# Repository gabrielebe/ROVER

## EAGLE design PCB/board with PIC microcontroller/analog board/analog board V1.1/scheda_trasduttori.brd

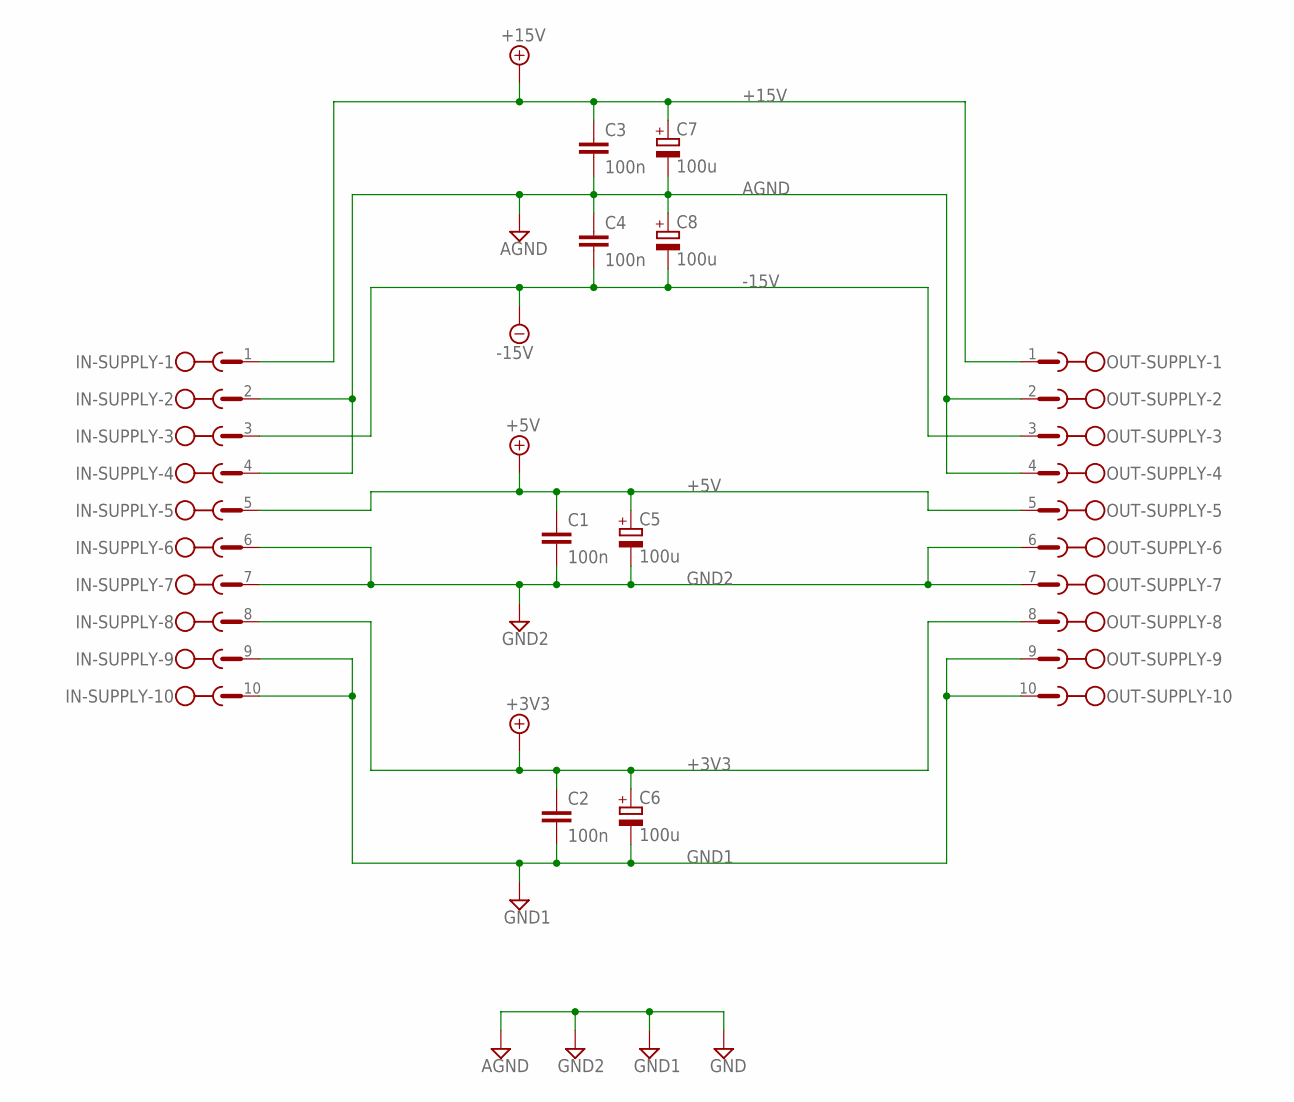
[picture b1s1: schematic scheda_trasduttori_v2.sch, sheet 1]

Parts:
C1, C2, C3, C4: 100n; C2.5-3
C5, C6, C7, C8: 100u; E2,5-7
IN-SUPPLY: MSTBA10
OUT-SUPPLY: MSTBA10

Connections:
+3V3: C2.1, C6.+, IN-SUPPLY.8, OUT-SUPPLY.8; also elsewhere on the board
+5V: C1.1, C5.+, IN-SUPPLY.5, OUT-SUPPLY.5; also elsewhere on the board
+15V: C3.1, C7.+, IN-SUPPLY.1, OUT-SUPPLY.1; also elsewhere on the board
-15V: C4.2, C8.-, IN-SUPPLY.3, OUT-SUPPLY.3; also elsewhere on the board
AGND: C3.2, C4.1, C7.-, C8.+, IN-SUPPLY.2, IN-SUPPLY.4, OUT-SUPPLY.2, OUT-SUPPLY.4; also elsewhere on the board
GND1: C2.2, C6.-, IN-SUPPLY.9, IN-SUPPLY.10, OUT-SUPPLY.9, OUT-SUPPLY.10; also elsewhere on the board
GND2: C1.2, C5.-, IN-SUPPLY.6, IN-SUPPLY.7, OUT-SUPPLY.6, OUT-SUPPLY.7; also elsewhere on the board

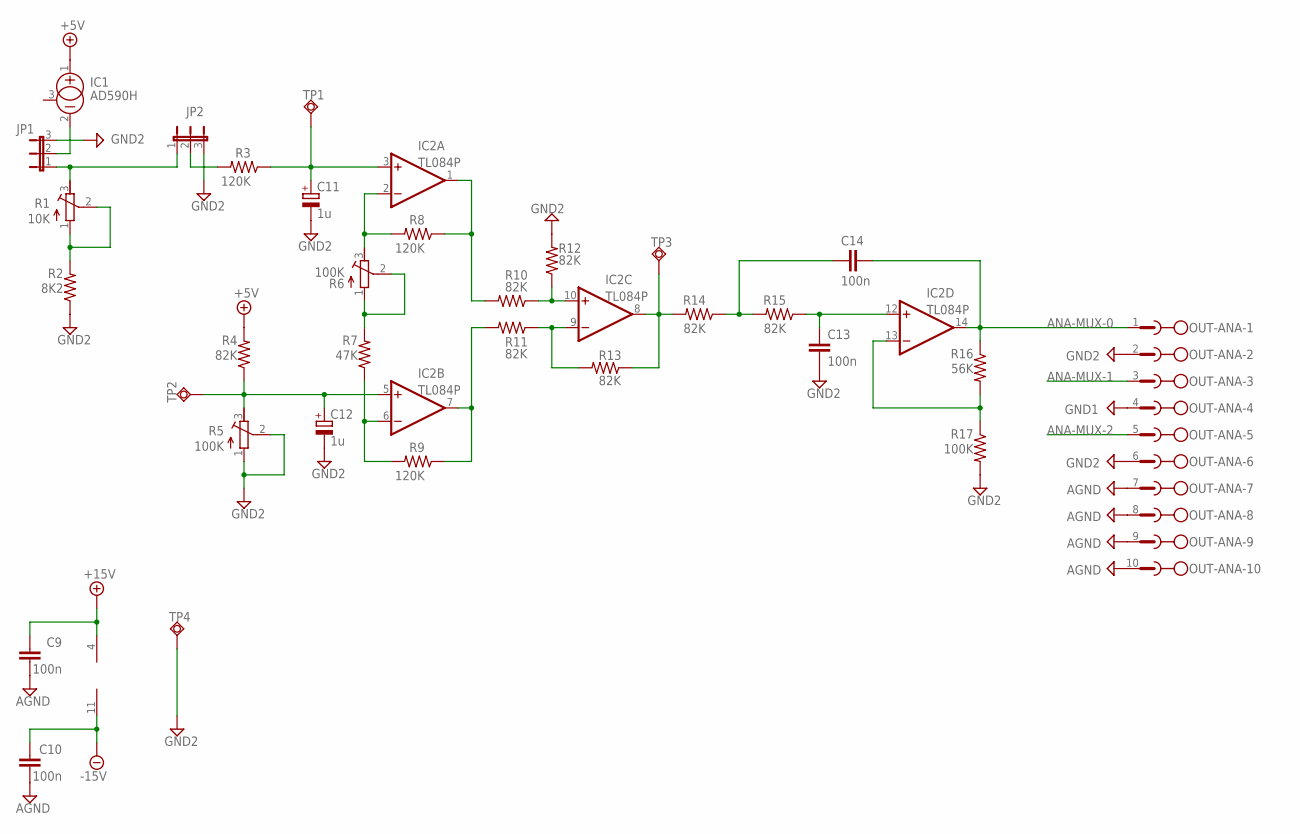
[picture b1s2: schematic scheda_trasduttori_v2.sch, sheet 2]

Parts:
C9, C10, C13, C14: 100n; C025-024X044
C11, C12: 1u; E5-8,5
IC1: AD590H; TO18
IC2: TL084P; DIL14
JP1, JP2: JP2E; JP2
OUT-ANA: MSTBA10
R1: 10K; RTRIM64W
R2: 8K2; 0204/7
R3, R8, R9: 120K; 0204/7
R4, R10, R11, R12, R13, R14, R15: 82K; 0204/7
R5, R6: 100K; RTRIM64W
R7: 47K; 0204/7
R16: 56K; 0204/7
R17: 100K; 0204/7
TP1, TP2, TP3, TP4: TPSQPAD1-17Y; P1-17Y

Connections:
+5V: IC1.1 (+), R4.2; also elsewhere on the board
+15V: C9.2, IC2.4 (V+); also elsewhere on the board
-15V: C10.2, IC2.11 (V-); also elsewhere on the board
AGND: C9.1, C10.1, OUT-ANA.7, OUT-ANA.8, OUT-ANA.9, OUT-ANA.10; also elsewhere on the board
ANA-MUX-0: C14.2, IC2.14 (OUT), OUT-ANA.1, R16.1
GND2: C11.-, C12.-, C13.1, JP1.3, JP2.3, OUT-ANA.2, OUT-ANA.6, R2.1, R5.1 (E), R5.2 (S), R12.2, R17.2, TP4.TP; also elsewhere on the board
unnamed: R1.1 (E), R1.2 (S), R2.2
unnamed: IC1.2 (-), JP1.2
unnamed: R6.1 (E), R6.2 (S), R7.2
unnamed 14: C11.+, IC2.3 (+IN), R3.1, TP1.TP; also elsewhere on the board
unnamed: IC2.2 (-IN), R6.3 (A), R8.2
unnamed: IC2.1 (OUT), R8.1, R10.2
unnamed: JP2.2, R3.2
unnamed: JP1.1, JP2.1, R1.3 (A)
unnamed 19: C12.+, IC2.5 (+IN), R4.1, R5.3 (A), TP2.TP; also elsewhere on the board
unnamed: IC2.6 (-IN), R7.1, R9.2
unnamed: IC2.7 (OUT), R9.1, R11.2
unnamed: IC2.10 (+IN), R10.1, R12.1
unnamed: IC2.9 (-IN), R11.1, R13.2
unnamed 24: IC2.8 (OUT), R13.1, R14.2, TP3.TP; also elsewhere on the board
unnamed: C14.1, R14.1, R15.2
unnamed: C13.2, IC2.12 (+IN), R15.1
unnamed: IC2.13 (-IN), R16.2, R17.1

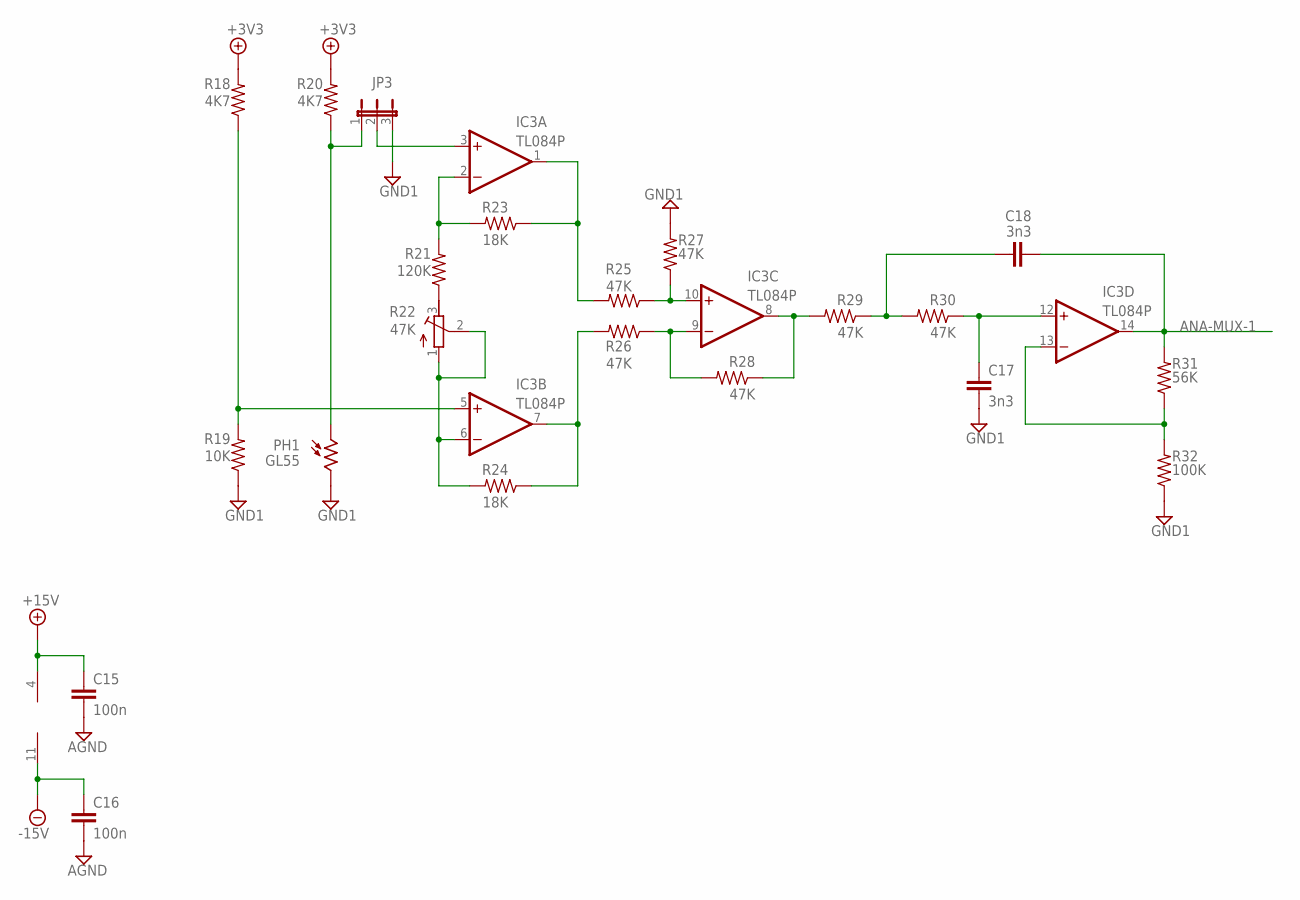
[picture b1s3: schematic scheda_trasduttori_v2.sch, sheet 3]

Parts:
C15, C16: 100n; C025-025X050
C17, C18: 3n3; C025-025X050
IC3: TL084P; DIL14
JP3: JP2E; JP2
PH1: GL55; T0-46-A10XX
R18, R20: 4K7; 0204/7
R19: 10K; 0204/7
R21: 120K; 0204/7
R22: 47K; RTRIM64W
R23, R24: 18K; 0204/7
R25, R26, R27, R28, R29, R30: 47K; 0204/7
R31: 56K; 0204/7
R32: 100K; 0204/7

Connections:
+4.1V: R18.2, R20.2
+15V: C15.1, IC3.4 (V+); also elsewhere on the board
-15V: C16.1, IC3.11 (V-); also elsewhere on the board
AGND: C15.2, C16.2; also elsewhere on the board
ANA-MUX-1: C18.2, IC3.14 (OUT), R31.2
GND1: C17.2, JP3.3, PH1.2, R19.1, R27.2, R32.1; also elsewhere on the board
unnamed: IC3.5 (+IN), R18.1, R19.2
unnamed: JP3.1, PH1.1, R20.1
unnamed: R21.1, R22.3 (A)
unnamed: IC3.6 (-IN), R22.1 (E), R22.2 (S), R24.2
unnamed: IC3.7 (OUT), R24.1, R26.2
unnamed: IC3.1 (OUT), R23.1, R25.2
unnamed: IC3.2 (-IN), R21.2, R23.2
unnamed: IC3.10 (+IN), R25.1, R27.1
unnamed: IC3.9 (-IN), R26.1, R28.2
unnamed: IC3.8 (OUT), R28.1, R29.2
unnamed: C17.1, IC3.12 (+IN), R30.1
unnamed: IC3.13 (-IN), R31.1, R32.2
unnamed: C18.1, R29.1, R30.2
unnamed: IC3.3 (+IN), JP3.2

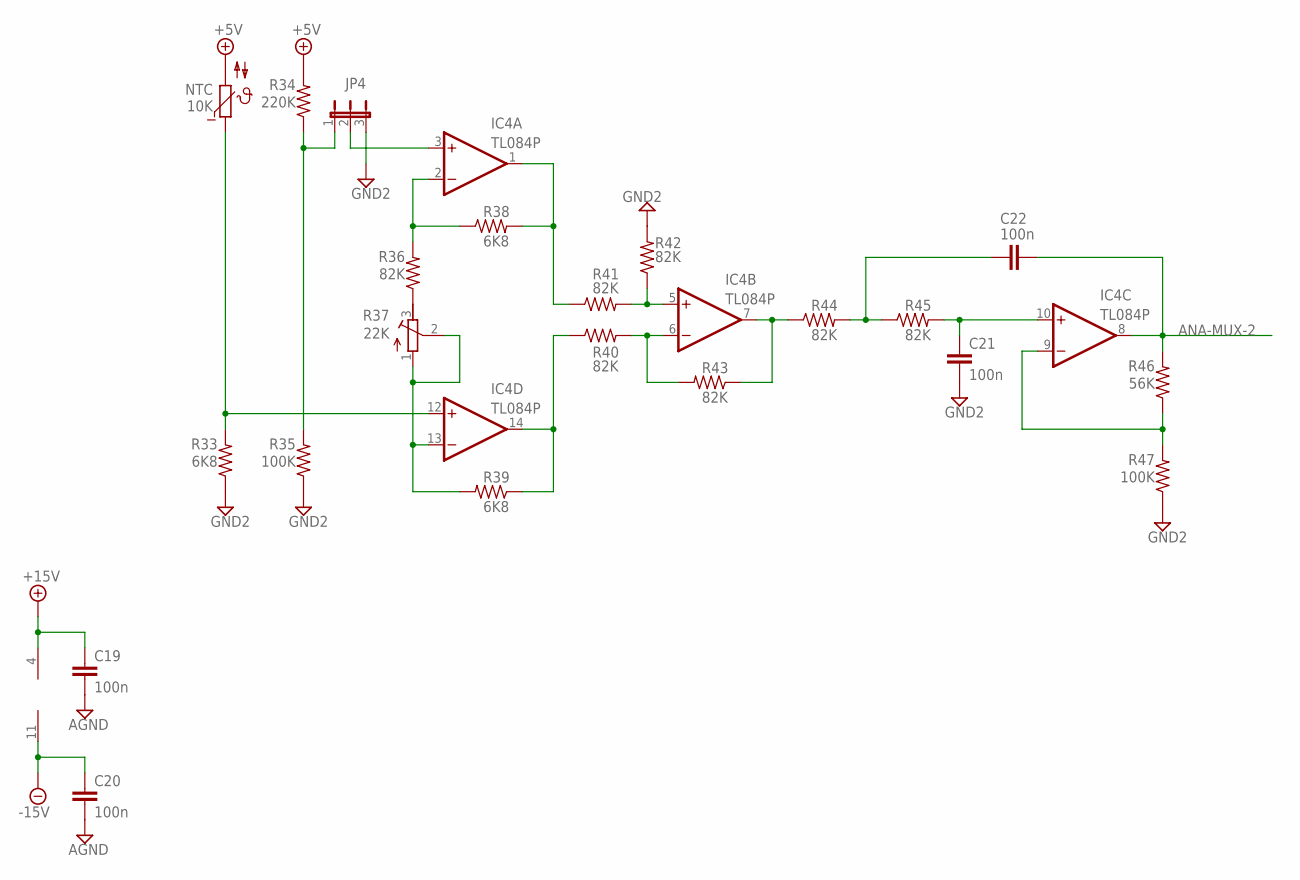
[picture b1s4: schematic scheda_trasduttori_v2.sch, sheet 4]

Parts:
C19, C20, C21, C22: 100n; C025-025X050
IC4: TL084P; DIL14
JP4: JP2E; JP2
NTC: 10K; P640
R33, R38, R39: 6K8; 0204/7
R34: 220K; 0204/7
R35, R47: 100K; 0204/7
R36, R40, R41, R42, R43, R44, R45: 82K; 0204/7
R37: 22K; RTRIM64W
R46: 56K; 0204/7

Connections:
+5V: NTC.2, R34.2; also elsewhere on the board
+15V: C19.1, IC4.4 (V+); also elsewhere on the board
-15V: C20.1, IC4.11 (V-); also elsewhere on the board
AGND: C19.2, C20.2; also elsewhere on the board
ANA-MUX-2: C22.2, IC4.8 (OUT), R46.2
GND2: C21.2, JP4.3, R33.1, R35.1, R42.2, R47.1; also elsewhere on the board
unnamed: C21.1, IC4.10 (+IN), R45.2
unnamed: IC4.9 (-IN), R46.1, R47.2
unnamed: C22.1, R44.2, R45.1
unnamed: IC4.12 (+IN), NTC.1, R33.2
unnamed: R36.1, R37.3 (A)
unnamed: IC4.2 (-IN), R36.2, R38.1
unnamed: IC4.1 (OUT), R38.2, R40.1
unnamed: IC4.13 (-IN), R37.1 (E), R37.2 (S), R39.2
unnamed: IC4.14 (OUT), R39.1, R41.1
unnamed: IC4.6 (-IN), R41.2, R43.2
unnamed: IC4.5 (+IN), R40.2, R42.1
unnamed: IC4.7 (OUT), R43.1, R44.1
unnamed: JP4.1, R34.1, R35.2
unnamed: IC4.3 (+IN), JP4.2

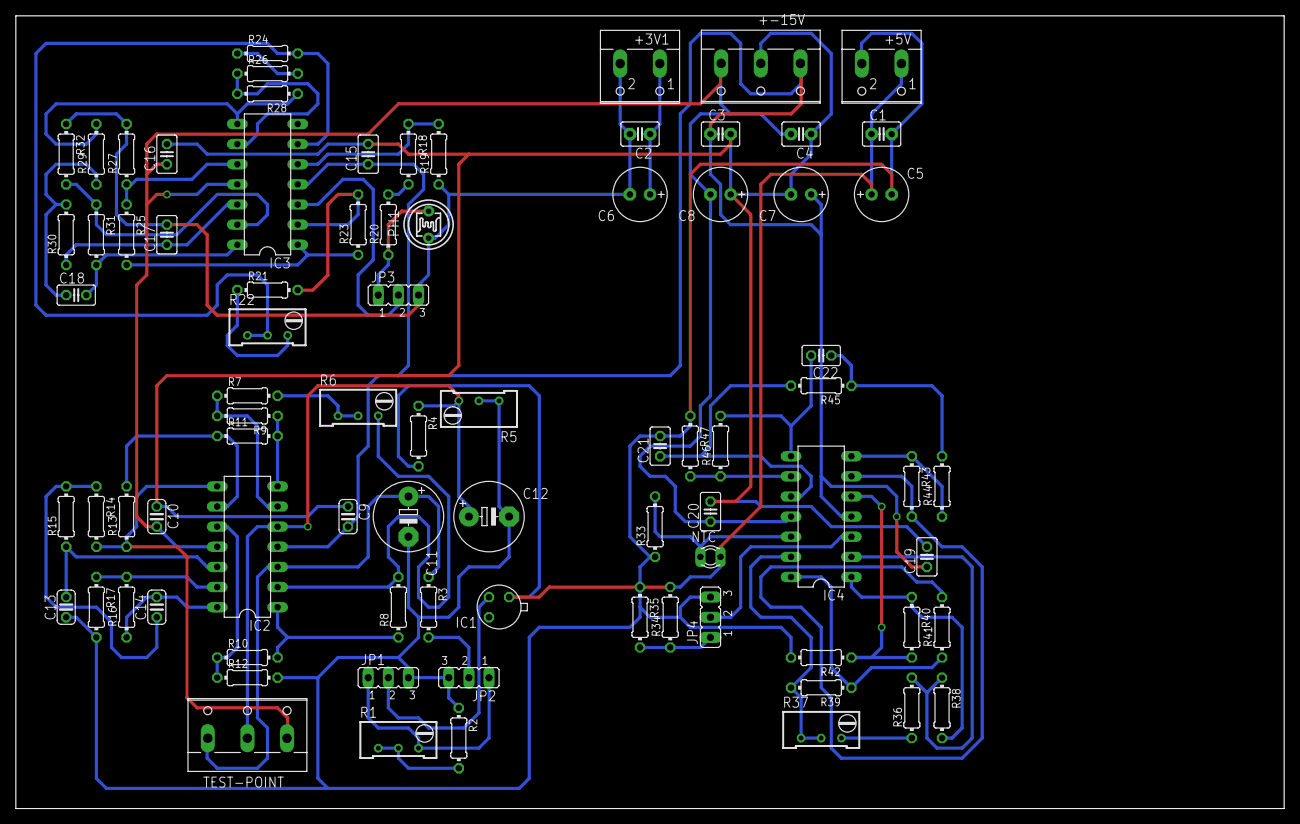
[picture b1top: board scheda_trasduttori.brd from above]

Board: 2 copper layers, 160.0 x 100.0 mm, 83 parts (0 on the bottom side), 56 nets.

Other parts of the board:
+3V1, +5V: W237-102
+-15V: W237-103
TEST-POINT: W237-103

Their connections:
+3V3: +3V1.1; also elsewhere on the board
+5V: +5V.1; also elsewhere on the board
+15V: +-15V.1; also elsewhere on the board
-15V: +-15V.3; also elsewhere on the board
AGND: +-15V.2; also elsewhere on the board
GND1: +3V1.2; also elsewhere on the board
GND2: +5V.2; also elsewhere on the board
unnamed 14: TEST-POINT.1; also elsewhere on the board
unnamed 19: TEST-POINT.2; also elsewhere on the board
unnamed 24: TEST-POINT.3; also elsewhere on the board

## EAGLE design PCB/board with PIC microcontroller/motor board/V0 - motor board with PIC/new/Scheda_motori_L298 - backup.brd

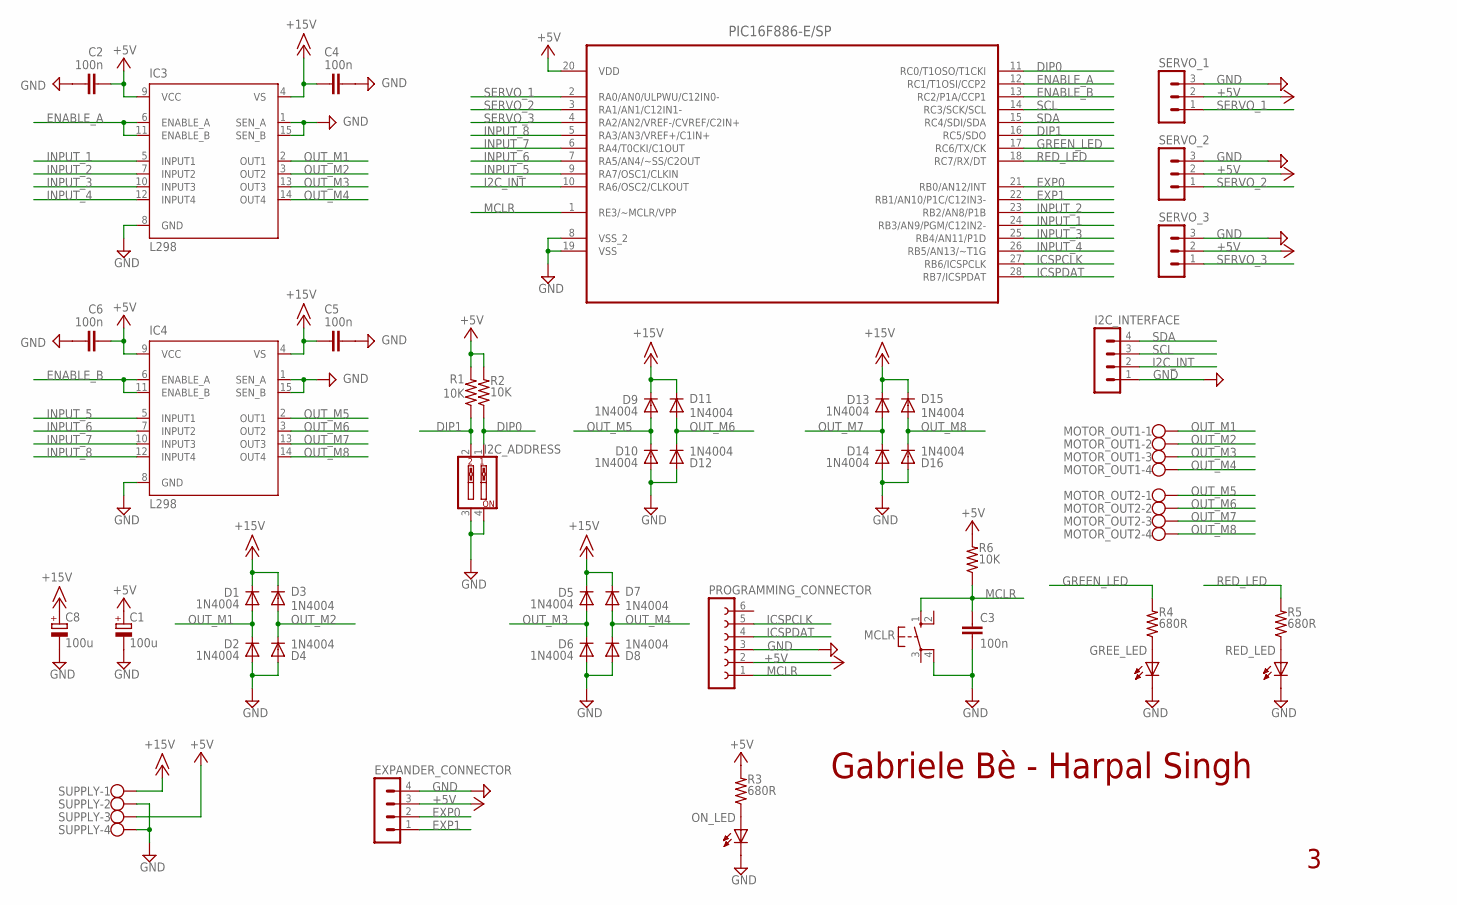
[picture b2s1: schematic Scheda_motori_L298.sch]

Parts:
C1, C8: 100u; E2,5-7
C2, C3, C4, C5, C6: 100n; C050-024X044
D1, D2, D3, D4, D5, D6, D7, D8, D9, D10, D11, D12, D13, D14, D15, D16: 1N4004; DO41-10
EXPANDER_CONNECTOR: MA04-1
GREE_LED: HLMP6
I2C_ADDRESS: SW_DIP-2; EDG-02
I2C_INTERFACE: MA04-1
IC3, IC4: L298; MULTIWATT-15
MCLR: 10-XX; B3F-10XX
MOTOR_OUT1, MOTOR_OUT2: W237-4
ON_LED: HLMP6
PROGRAMMING_CONNECTOR: FE06-1; FE06
R1, R2, R6: 10K; 0207/10
R3, R4, R5: 680R; 0207/10
RED_LED: HLMP6
SERVO_1, SERVO_2, SERVO_3: MA03-1
SUPPLY: W237-4
U$1: PIC16F886-E/SP; DIP254P762X508-28

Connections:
+5V: C1.+, C2.2, C6.2, EXPANDER_CONNECTOR.3, IC3.9 (VCC), IC4.9 (VCC), PROGRAMMING_CONNECTOR.2, R1.2, R2.2, R3.2, R6.2, SERVO_1.2, SERVO_2.2, SERVO_3.2, SUPPLY.3, U$1.20 (VDD)
+15V: C4.1, C5.1, C8.+, D1.C, D3.C, D5.C, D7.C, D9.C, D11.C, D13.C, D15.C, IC3.4 (VS), IC4.4 (VS), SUPPLY.1
DIP0: I2C_ADDRESS.1, R2.1, U$1.11 (RC0/T1OSO/T1CKI)
DIP1: I2C_ADDRESS.2, R1.1, U$1.16 (RC5/SDO)
ENABLE_A: IC3.6 (ENABLE_A), IC3.11 (ENABLE_B), U$1.12 (RC1/T1OSI/CCP2)
ENABLE_B: IC4.6 (ENABLE_A), IC4.11 (ENABLE_B), U$1.13 (RC2/P1A/CCP1)
EXP0: EXPANDER_CONNECTOR.2, U$1.21 (RB0/AN12/INT)
EXP1: EXPANDER_CONNECTOR.1, U$1.22 (RB1/AN10/P1C/C12IN3-)
GND: C1.-, C2.1, C3.2, C4.2, C5.2, C6.1, C8.-, D2.A, D4.A, D6.A, D8.A, D10.A, D12.A, D14.A, D16.A, EXPANDER_CONNECTOR.4, GREE_LED.K, I2C_ADDRESS.3, I2C_ADDRESS.4, I2C_INTERFACE.1, IC3.1 (SEN_A), IC3.8 (GND), IC3.15 (SEN_B), IC4.1 (SEN_A), IC4.8 (GND), IC4.15 (SEN_B), MCLR.4 (P1), ON_LED.K, PROGRAMMING_CONNECTOR.3, RED_LED.K, SERVO_1.3, SERVO_2.3, SERVO_3.3, SUPPLY.2, SUPPLY.4, U$1.8 (VSS_2), U$1.19 (VSS)
GREEN_LED: R4.2, U$1.17 (RC6/TX/CK)
I2C_INT: I2C_INTERFACE.2, U$1.10 (RA6/OSC2/CLKOUT)
ICSPCLK: PROGRAMMING_CONNECTOR.5, U$1.27 (RB6/ICSPCLK)
ICSPDAT: PROGRAMMING_CONNECTOR.4, U$1.28 (RB7/ICSPDAT)
INPUT_1: IC3.5 (INPUT1), U$1.24 (RB3/AN9/PGM/C12IN2-)
INPUT_2: IC3.7 (INPUT2), U$1.23 (RB2/AN8/P1B)
INPUT_3: IC3.10 (INPUT3), U$1.25 (RB4/AN11/P1D)
INPUT_4: IC3.12 (INPUT4), U$1.26 (RB5/AN13/~T1G)
INPUT_5: IC4.5 (INPUT1), U$1.9 (RA7/OSC1/CLKIN)
INPUT_6: IC4.7 (INPUT2), U$1.7 (RA5/AN4/~SS/C2OUT)
INPUT_7: IC4.10 (INPUT3), U$1.6 (RA4/T0CKI/C1OUT)
INPUT_8: IC4.12 (INPUT4), U$1.5 (RA3/AN3/VREF+/C1IN+)
MCLR: C3.1, MCLR.1 (S), PROGRAMMING_CONNECTOR.1, R6.1, U$1.1 (RE3/~MCLR/VPP)
unnamed: ON_LED.A, R3.1
unnamed: GREE_LED.A, R4.1
unnamed: R5.1, RED_LED.A
OUT_M1: D1.A, D2.C, IC3.2 (OUT1), MOTOR_OUT1.1
OUT_M2: D3.A, D4.C, IC3.3 (OUT2), MOTOR_OUT1.2
OUT_M3: D5.A, D6.C, IC3.13 (OUT3), MOTOR_OUT1.3
OUT_M4: D7.A, D8.C, IC3.14 (OUT4), MOTOR_OUT1.4
OUT_M5: D9.A, D10.C, IC4.2 (OUT1), MOTOR_OUT2.1
OUT_M6: D11.A, D12.C, IC4.3 (OUT2), MOTOR_OUT2.2
OUT_M7: D13.A, D14.C, IC4.13 (OUT3), MOTOR_OUT2.3
OUT_M8: D15.A, D16.C, IC4.14 (OUT4), MOTOR_OUT2.4
RED_LED: R5.2, U$1.18 (RC7/RX/DT)
SCL: I2C_INTERFACE.3, U$1.14 (RC3/SCK/SCL)
SDA: I2C_INTERFACE.4, U$1.15 (RC4/SDI/SDA)
SERVO_1: SERVO_1.1, U$1.2 (RA0/AN0/ULPWU/C12IN0-)
SERVO_2: SERVO_2.1, U$1.3 (RA1/AN1/C12IN1-)
SERVO_3: SERVO_3.1, U$1.4 (RA2/AN2/VREF-/CVREF/C2IN+)

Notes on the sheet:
Gabriele Bè - Harpal Singh

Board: 2 copper layers, 46 parts (0 on the bottom side), 39 nets, no tracks yet.

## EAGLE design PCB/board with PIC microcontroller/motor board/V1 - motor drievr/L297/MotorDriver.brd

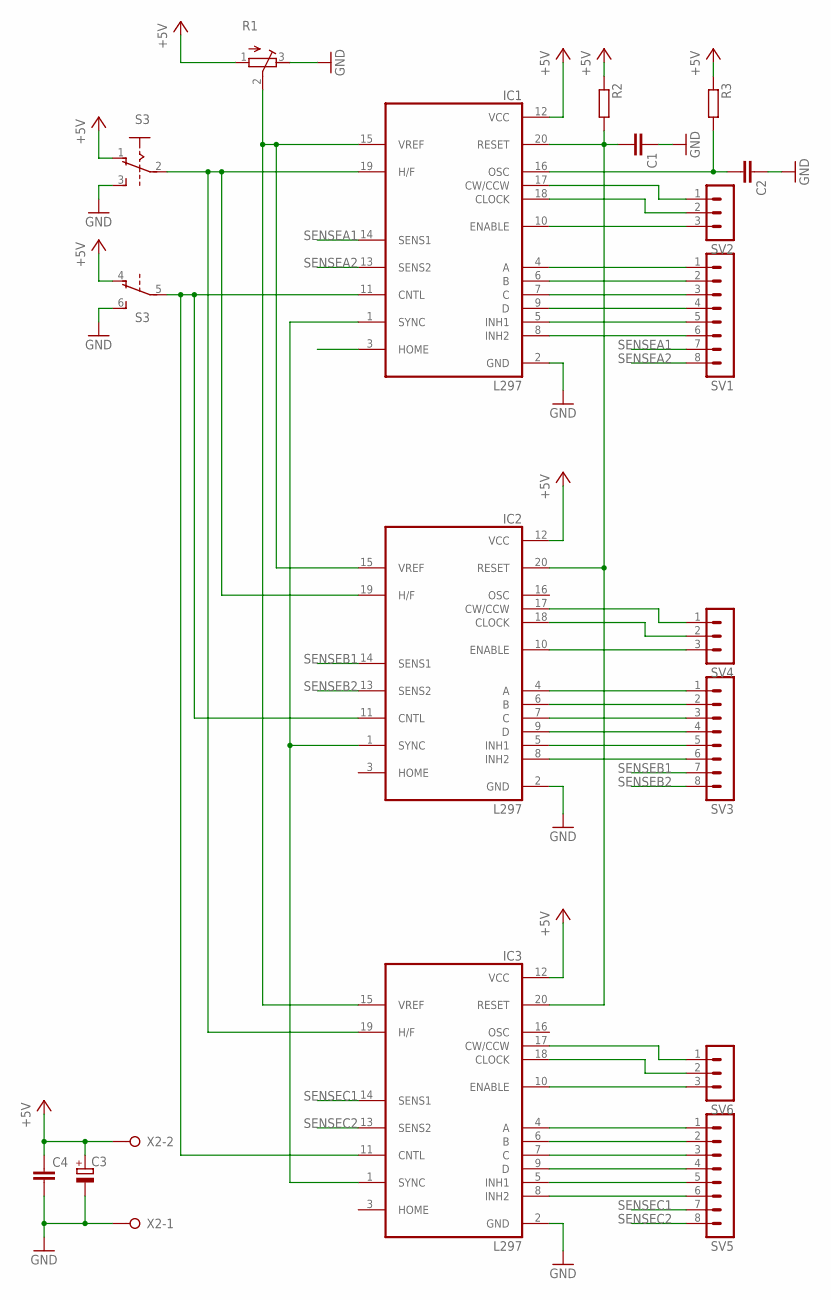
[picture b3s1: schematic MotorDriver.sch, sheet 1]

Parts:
C1, C2, C4: C-EU050-024X044; C050-024X044
C3: CPOL-EUE3.5-8; E3,5-8
IC1, IC2, IC3: L297; DIL20
R1: R-TRIMM64P; RTRIM64P
R2, R3: R-EU_0207/10; 0207/10
S3: A68-A31
SV1, SV3, SV5: MA08-1
SV2, SV4, SV6: MA03-1
X2: W237-02P; W237-132

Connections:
+5V: C3.+, C4.1, IC1.12 (VCC), IC2.12 (VCC), IC3.12 (VCC), R1.1 (A), R2.1, R3.1, S3.1 (O), S3.4 (O), X2.2
GND: C1.1, C2.1, C3.-, C4.2, IC1.2 (GND), IC2.2 (GND), IC3.2 (GND), R1.3 (E), S3.3 (S), S3.6 (S), X2.1
unnamed: C2.2, IC1.16 (OSC), R3.2
unnamed: IC1.4 (A), SV1.1
unnamed: IC1.6 (B), SV1.2
unnamed: IC1.7 (C), SV1.3
unnamed: IC1.9 (D), SV1.4
unnamed: IC1.5 (INH1), SV1.5
unnamed: IC1.8 (INH2), SV1.6
unnamed: IC1.17 (CW/CCW), SV2.1
unnamed: IC1.18 (CLOCK), SV2.2
unnamed: IC1.10 (ENABLE), SV2.3
unnamed: IC1.19 (H/F), IC2.19 (H/F), IC3.19 (H/F), S3.2
unnamed: IC1.11 (CNTL), IC2.11 (CNTL), IC3.11 (CNTL), S3.5
unnamed: IC1.15 (VREF), IC2.15 (VREF), IC3.15 (VREF), R1.2 (S)
unnamed: IC2.4 (A), SV3.1
unnamed: IC2.6 (B), SV3.2
unnamed: IC2.7 (C), SV3.3
unnamed: IC2.9 (D), SV3.4
unnamed: IC2.5 (INH1), SV3.5
unnamed: IC2.8 (INH2), SV3.6
unnamed: IC2.17 (CW/CCW), SV4.1
unnamed: IC2.18 (CLOCK), SV4.2
unnamed: IC2.10 (ENABLE), SV4.3
unnamed: IC1.1 (SYNC), IC2.1 (SYNC), IC3.1 (SYNC)
unnamed: C1.2, IC1.20 (RESET), IC2.20 (RESET), IC3.20 (RESET), R2.2
unnamed: IC3.4 (A), SV5.1
unnamed: IC3.6 (B), SV5.2
unnamed: IC3.7 (C), SV5.3
unnamed: IC3.9 (D), SV5.4
unnamed: IC3.5 (INH1), SV5.5
unnamed: IC3.8 (INH2), SV5.6
unnamed: IC3.17 (CW/CCW), SV6.1
unnamed: IC3.18 (CLOCK), SV6.2
unnamed: IC3.10 (ENABLE), SV6.3
SENSEA1: IC1.14 (SENS1), SV1.7
SENSEA2: IC1.13 (SENS2), SV1.8
SENSEB1: IC2.14 (SENS1), SV3.7
SENSEB2: IC2.13 (SENS2), SV3.8
SENSEC1: IC3.14 (SENS1), SV5.7
SENSEC2: IC3.13 (SENS2), SV5.8

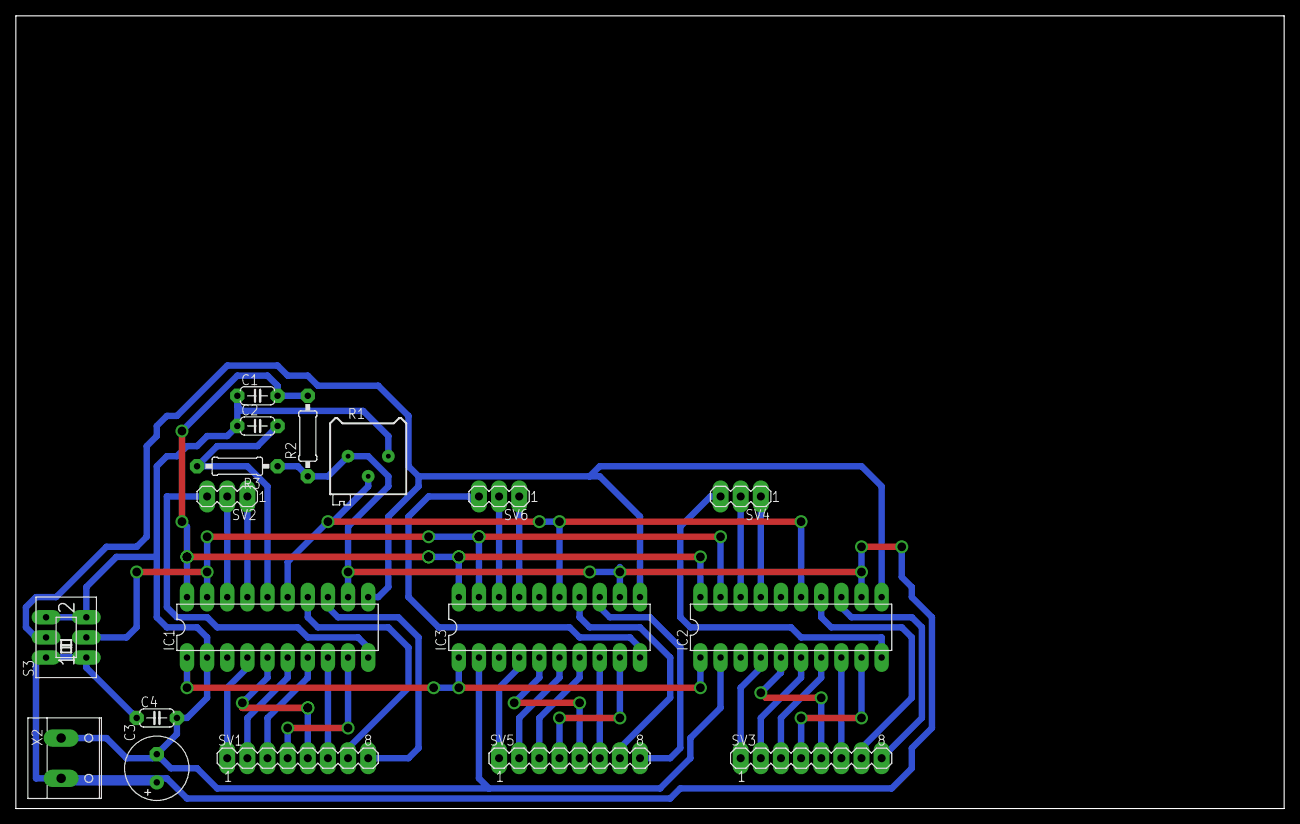
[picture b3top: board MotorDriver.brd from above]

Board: 2 copper layers, 160.0 x 100.0 mm, 18 parts (0 on the bottom side), 41 nets.

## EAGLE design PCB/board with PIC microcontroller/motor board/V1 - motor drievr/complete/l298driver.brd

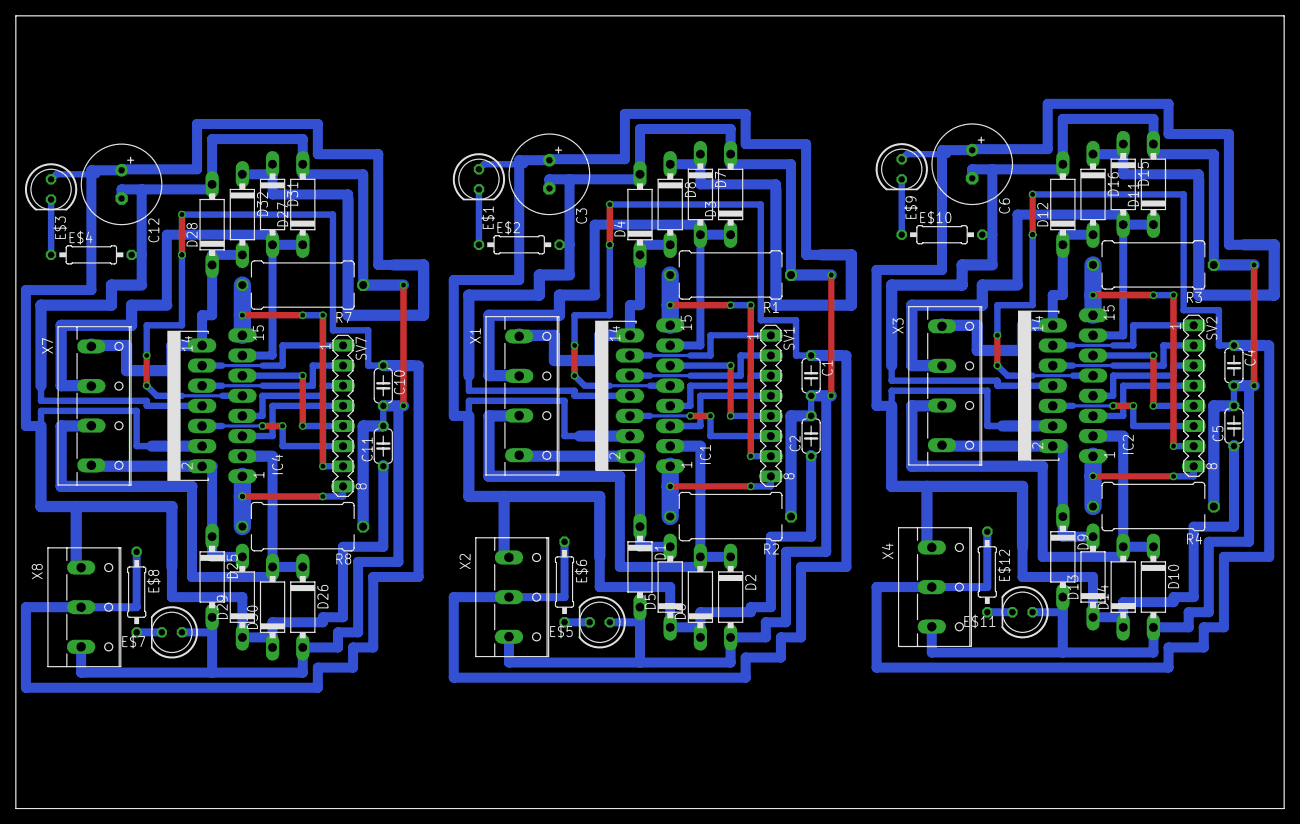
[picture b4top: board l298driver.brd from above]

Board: 2 copper layers, 160.0 x 100.0 mm, 63 parts (0 on the bottom side), 51 nets.

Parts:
C1, C2, C4, C5, C10, C11: C050-024X044
C3, C6, C12: E3,5-10
D1, D2, D3, D4, D5, D6, D7, D8, D9, D10, D11, D12, D13, D14, D15, D16, D25, D26, D27, D28, D29, D30, D31, D32: BA157; P1-10
E$1, E$3, E$5, E$7, E$9, E$11: LED5MM
E$2, E$4, E$6, E$8, E$10, E$12: 0207/10
IC1, IC2, IC4: L298; MULTIWATT-15
R1, R2, R3, R4, R7, R8: RDH/15
SV1, SV2, SV7: MA08-1
X1, X3, X7: W237-4
X2, X4, X8: W237-103

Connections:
GND1: C1.2, C2.2, C3.-, D1.A, D2.A, D3.A, D4.A, E$2.2, E$5.A, IC1.8, R1.1, R2.1, X2.3
GND2: C4.2, C5.2, C6.-, D9.A, D10.A, D11.A, D12.A, E$10.2, E$11.A, IC2.8, R3.1, R4.1, X4.3
GND3: C10.2, C11.2, C12.-, D25.A, D26.A, D27.A, D28.A, E$4.2, E$7.A, IC4.8, R7.1, R8.1, X8.3
unnamed: D1.C, D5.A, IC1.2, X1.4
unnamed: D2.C, D6.A, IC1.3, X1.3
unnamed: D3.C, D7.A, IC1.13, X1.2
unnamed: D4.C, D8.A, IC1.14, X1.1
unnamed: IC1.12, SV1.1
unnamed: IC1.10, SV1.2
unnamed: IC1.7, SV1.3
unnamed: IC1.5, SV1.4
unnamed: IC1.11, SV1.5
unnamed: IC1.6, SV1.6
unnamed: D9.C, D13.A, IC2.2, X3.4
unnamed: D10.C, D14.A, IC2.3, X3.3
unnamed: D11.C, D15.A, IC2.13, X3.2
unnamed: D12.C, D16.A, IC2.14, X3.1
unnamed: IC2.12, SV2.1
unnamed: IC2.10, SV2.2
unnamed: IC2.7, SV2.3
unnamed: IC2.5, SV2.4
unnamed: IC2.11, SV2.5
unnamed: IC2.6, SV2.6
unnamed: D25.C, D29.A, IC4.2, X7.4
unnamed: D26.C, D30.A, IC4.3, X7.3
unnamed: D27.C, D31.A, IC4.13, X7.2
unnamed: D28.C, D32.A, IC4.14, X7.1
unnamed: IC4.12, SV7.1
unnamed: IC4.10, SV7.2
unnamed: IC4.7, SV7.3
unnamed: IC4.5, SV7.4
unnamed: IC4.11, SV7.5
unnamed: IC4.6, SV7.6
S$1: E$1.K, E$2.1
S$2: E$3.K, E$4.1
S$3: E$5.K, E$6.2
S$4: E$7.K, E$8.2
S$5: E$9.K, E$10.1
S$6: E$11.K, E$12.2
SENSE1: IC1.1, R2.2, SV1.8
SENSE2: IC1.15, R1.2, SV1.7
SENSE3: IC2.1, R4.2, SV2.8
SENSE4: IC2.15, R3.2, SV2.7
SENSE7: IC4.1, R8.2, SV7.8
SENSE8: IC4.15, R7.2, SV7.7
VCC1: C1.1, E$6.1, IC1.9, X2.2
VCC2: C4.1, E$12.1, IC2.9, X4.2
VCC3: C10.1, E$8.1, IC4.9, X8.2
VDD1: C2.1, C3.+, D5.C, D6.C, D7.C, D8.C, E$1.A, IC1.4, X2.1
VDD2: C5.1, C6.+, D13.C, D14.C, D15.C, D16.C, E$9.A, IC2.4, X4.1
VDD3: C11.1, C12.+, D29.C, D30.C, D31.C, D32.C, E$3.A, IC4.4, X8.1
